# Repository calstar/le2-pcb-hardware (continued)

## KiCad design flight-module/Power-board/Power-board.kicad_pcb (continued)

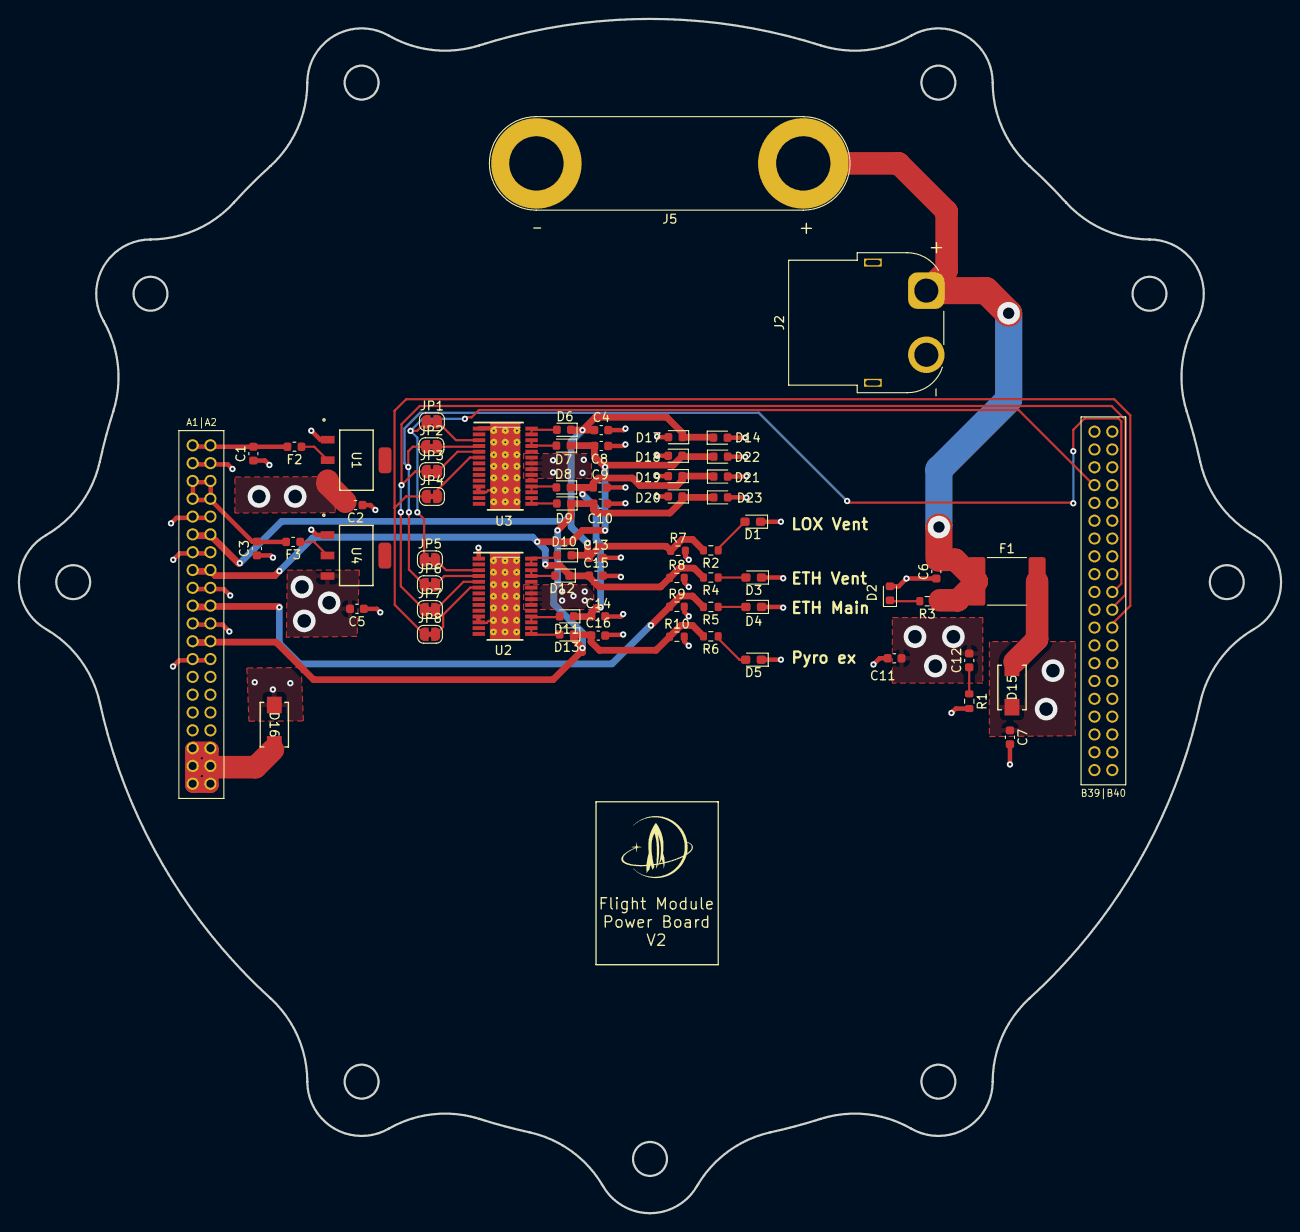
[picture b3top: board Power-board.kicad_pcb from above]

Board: 4 copper layers, 141.7 x 134.1 mm, 67 parts (0 on the bottom side), 40 nets.

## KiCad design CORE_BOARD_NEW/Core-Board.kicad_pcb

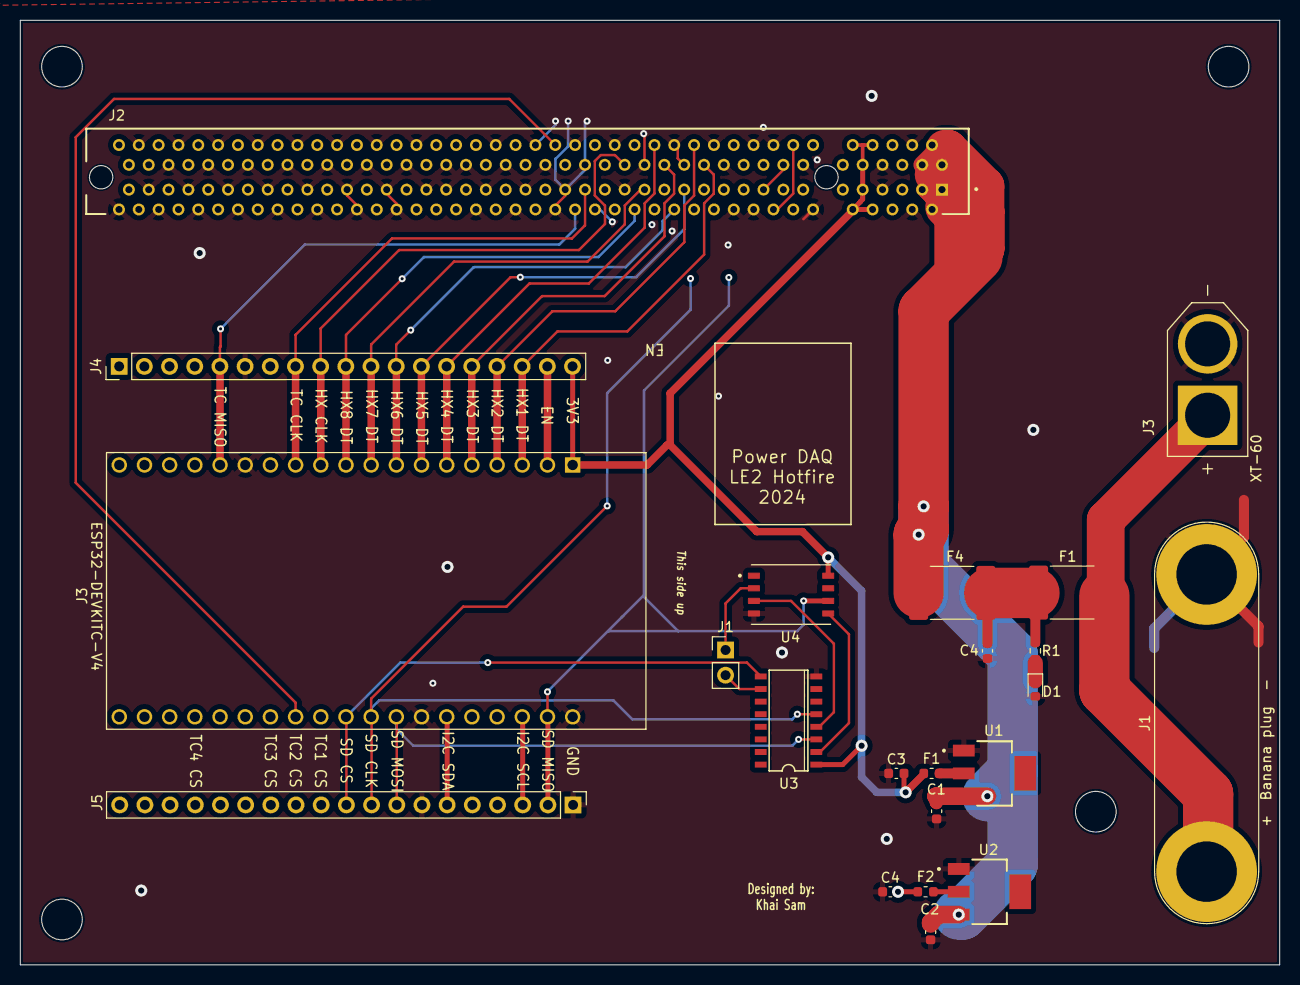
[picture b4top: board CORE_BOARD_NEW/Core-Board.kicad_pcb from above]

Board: 4 copper layers, 127.0 x 95.2 mm, 22 parts (0 on the bottom side), 35 nets.

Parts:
C1, C2: 10uF; C_0603_1608Metric
C3, C4, C4#2: 22uF; C_0603_1608Metric
D1: D_Small; D_0603_1608Metric
F1, F2: 500mA Fuse; Fuse_0603_1608Metric
F1#2, F4: 6A Fuse; Fuse_2920_7451Metric
J1: POWER; Banana_Jack_2Pin
J1#2: Pin Jumper; PinHeader_1x02_P2.54mm_Vertical
J2: Bus_PCI_Express_x16; SAMTEC_PCIE-164-02-F-D-TH-TR
J3: ESP32-DEVKITC-32D; MODULE_ESP32-DEVKITC-32D
J3#2: XT60-M; AMASS_XT60-M
J4, J5: Conn_01x19_Male; PinHeader_1x19_P2.54mm_Vertical
R1: 10k; R_0603_1608Metric
U1: AZ1117IH-3.3TRG1; SOT230P700X185-4N
U2: AZ1117IH-5TRG1; SOT230P700X185-4N
U3: 74HC4050D; SO16
U4: XTSD04GLGEAG; SON127P600X800X95-8N

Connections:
3.3V: C3.2, F1.2, J2.A8 (3.3V), J2.A9 (+3.3V), J2.A10 (3.3VAux), J2.B8 (+3.3V), J2.B9 (3.3V), J2.B10 (3.3Vaux), J3.1 (3V3), J4.19, U3.1 (VCC), U4.8 (VDD)
5V: C4.2, F2.2, J2.A5 (5V), J2.A6 (5V), J2.B5 (5V), J2.B6 (5V), J3.19 (EXT_5V), J4.1
12V: C1.2, C2.2, F4.2, J2.A1 (+12V), J2.A2 (+12V), J2.A3 (+12V), J2.B1 (+12V), J2.B2 (+12V), J2.B3 (+12V), U1.3 (INPUT), U2.3 (INPUT)
+12V: F1#2.1, J1.1, J3#2.P (POS)
EN: J3.2 (EN), J4.18
GND: C1.1, C2.1, C3.1, C4.1, C4#2.1, D1.2 (A), J1.2, J2.A4 (GND), J2.A7 (GND), J2.A12 (GND), J2.A15 (GND), J2.A18 (GND), J2.A20 (GND), J2.A23 (GND), J2.A24 (GND), J2.A27 (GND), J2.A28 (GND), J2.A31 (GND), J2.A34 (GND), J2.A37 (GND), J2.A38 (GND), J2.A41 (GND), J2.A42 (GND), J2.A45 (GND), J2.A46 (GND), J2.A49 (GND), J2.A51 (GND), J2.A54 (GND), J2.A55 (GND), J2.A58 (GND), J2.A59 (GND), J2.A62 (GND), J2.A63 (GND), J2.A66 (GND), J2.A67 (GND), J2.A70 (GND), J2.A71 (GND), J2.A74 (GND), J2.A75 (GND), J2.A78 (GND), J2.A79 (GND), J2.A82 (GND), J2.B4 (GND), J2.B7 (GND), J2.B13 (GND), J2.B16 (GND), J2.B18 (GND), J2.B21 (GND), J2.B22 (GND), J2.B25 (GND), J2.B26 (GND), J2.B29 (GND), J2.B32 (GND), J2.B35 (GND), J2.B36 (GND), J2.B39 (GND), J2.B40 (GND), J2.B43 (GND), J2.B44 (GND), J2.B47 (GND), J2.B49 (GND), J2.B52 (GND), J2.B53 (GND), J2.B56 (GND), J2.B57 (GND), J2.B60 (GND), J2.B61 (GND), J2.B64 (GND), J2.B65 (GND), J2.B68 (GND), J2.B69 (GND), J2.B72 (GND), J2.B73 (GND), J2.B76 (GND), J2.B77 (GND), J2.B80 (GND), J3.14 (GND1), J3.20 (GND3), J3.26 (GND2), J3#2.N (NEG), J4.6, J5.1, J5.7, U1.1 (GND), U2.1 (GND), U3.8 (GND), U4.4 (VSS)
HX1: J2.B23 (HX_DT1), J3.3 (SENSOR_VP), J4.17
HX2: J2.B24 (HX_DT2), J3.4 (SENSOR_VN), J4.16
HX3: J2.B27 (HX_DT3), J3.5 (IO34), J4.15
HX4: J2.B28 (HX_DT4), J3.6 (IO35), J4.14
HX5: J2.A25 (HX_DT5), J3.7 (IO32), J4.13
HX6: J2.A26 (HX_DT6), J3.8 (IO33), J4.12
HX7: J2.A29 (HX_DT7), J3.9 (IO25), J4.11
HX8: J2.A30 (HX_DT8), J3.10 (IO26), J4.10
HX CLK: J2.B31 (HX_CLK), J3.11 (IO27), J4.9
I2C SCL: J2.A16 (I2C_SCL_AUX), J2.B14 (I2C_SCL), J3.22 (IO22), J5.3
I2C SDA: J2.A17 (I2C_SDA_AUX), J2.B15 (I2C_SDA), J3.25 (IO21), J5.6
unnamed: C4#2.2, F1#2.2, F4.1, R1.1
unnamed: D1.1 (K), R1.2
unnamed: J1#2.1, U4.2 (SD3/~CS)
unnamed: F1.1, U1.2 (OUTPUT)
unnamed: F2.1, U2.2 (OUTPUT)
SD CLK_3.3: U3.4 (2Y), U4.3 (CLK)
SD CS_3.3: J1#2.2, U3.10 (4Y)
SD MOSI_3.3: U3.2 (1Y), U4.5 (CMD/DI)
SPI0 CLK: J2.B33 (SPI0_CLK), J3.28 (IO18), J5.9, U3.5 (2A)
SPI0 CS: J3.29 (IO5), J5.10, U3.9 (4A)
SPI0 MISO: J2.B34 (SPI0_MISO), J3.21 (IO23), J5.2, U4.6 (SD0/DO)
SPI0 MOSI: J3.27 (IO19), J5.8, U3.3 (1A)
SPI1 CLK: J2.A35 (SPI1_CLK), J3.12 (IO14), J4.8
SPI1 MISO: J2.A36 (SPI1_MISO), J3.15 (IO13), J4.5
TC CS 1: J2.B37 (TC_CS1), J3.30 (IO17)
TC CS 2: J2.B38 (TC_CS2), J3.31 (IO16)
TC CS 3: J2.A39 (TC_CS3), J3.32 (IO4)
TC CS 4: J2.A40 (TC_CS4), J3.35 (IO15)

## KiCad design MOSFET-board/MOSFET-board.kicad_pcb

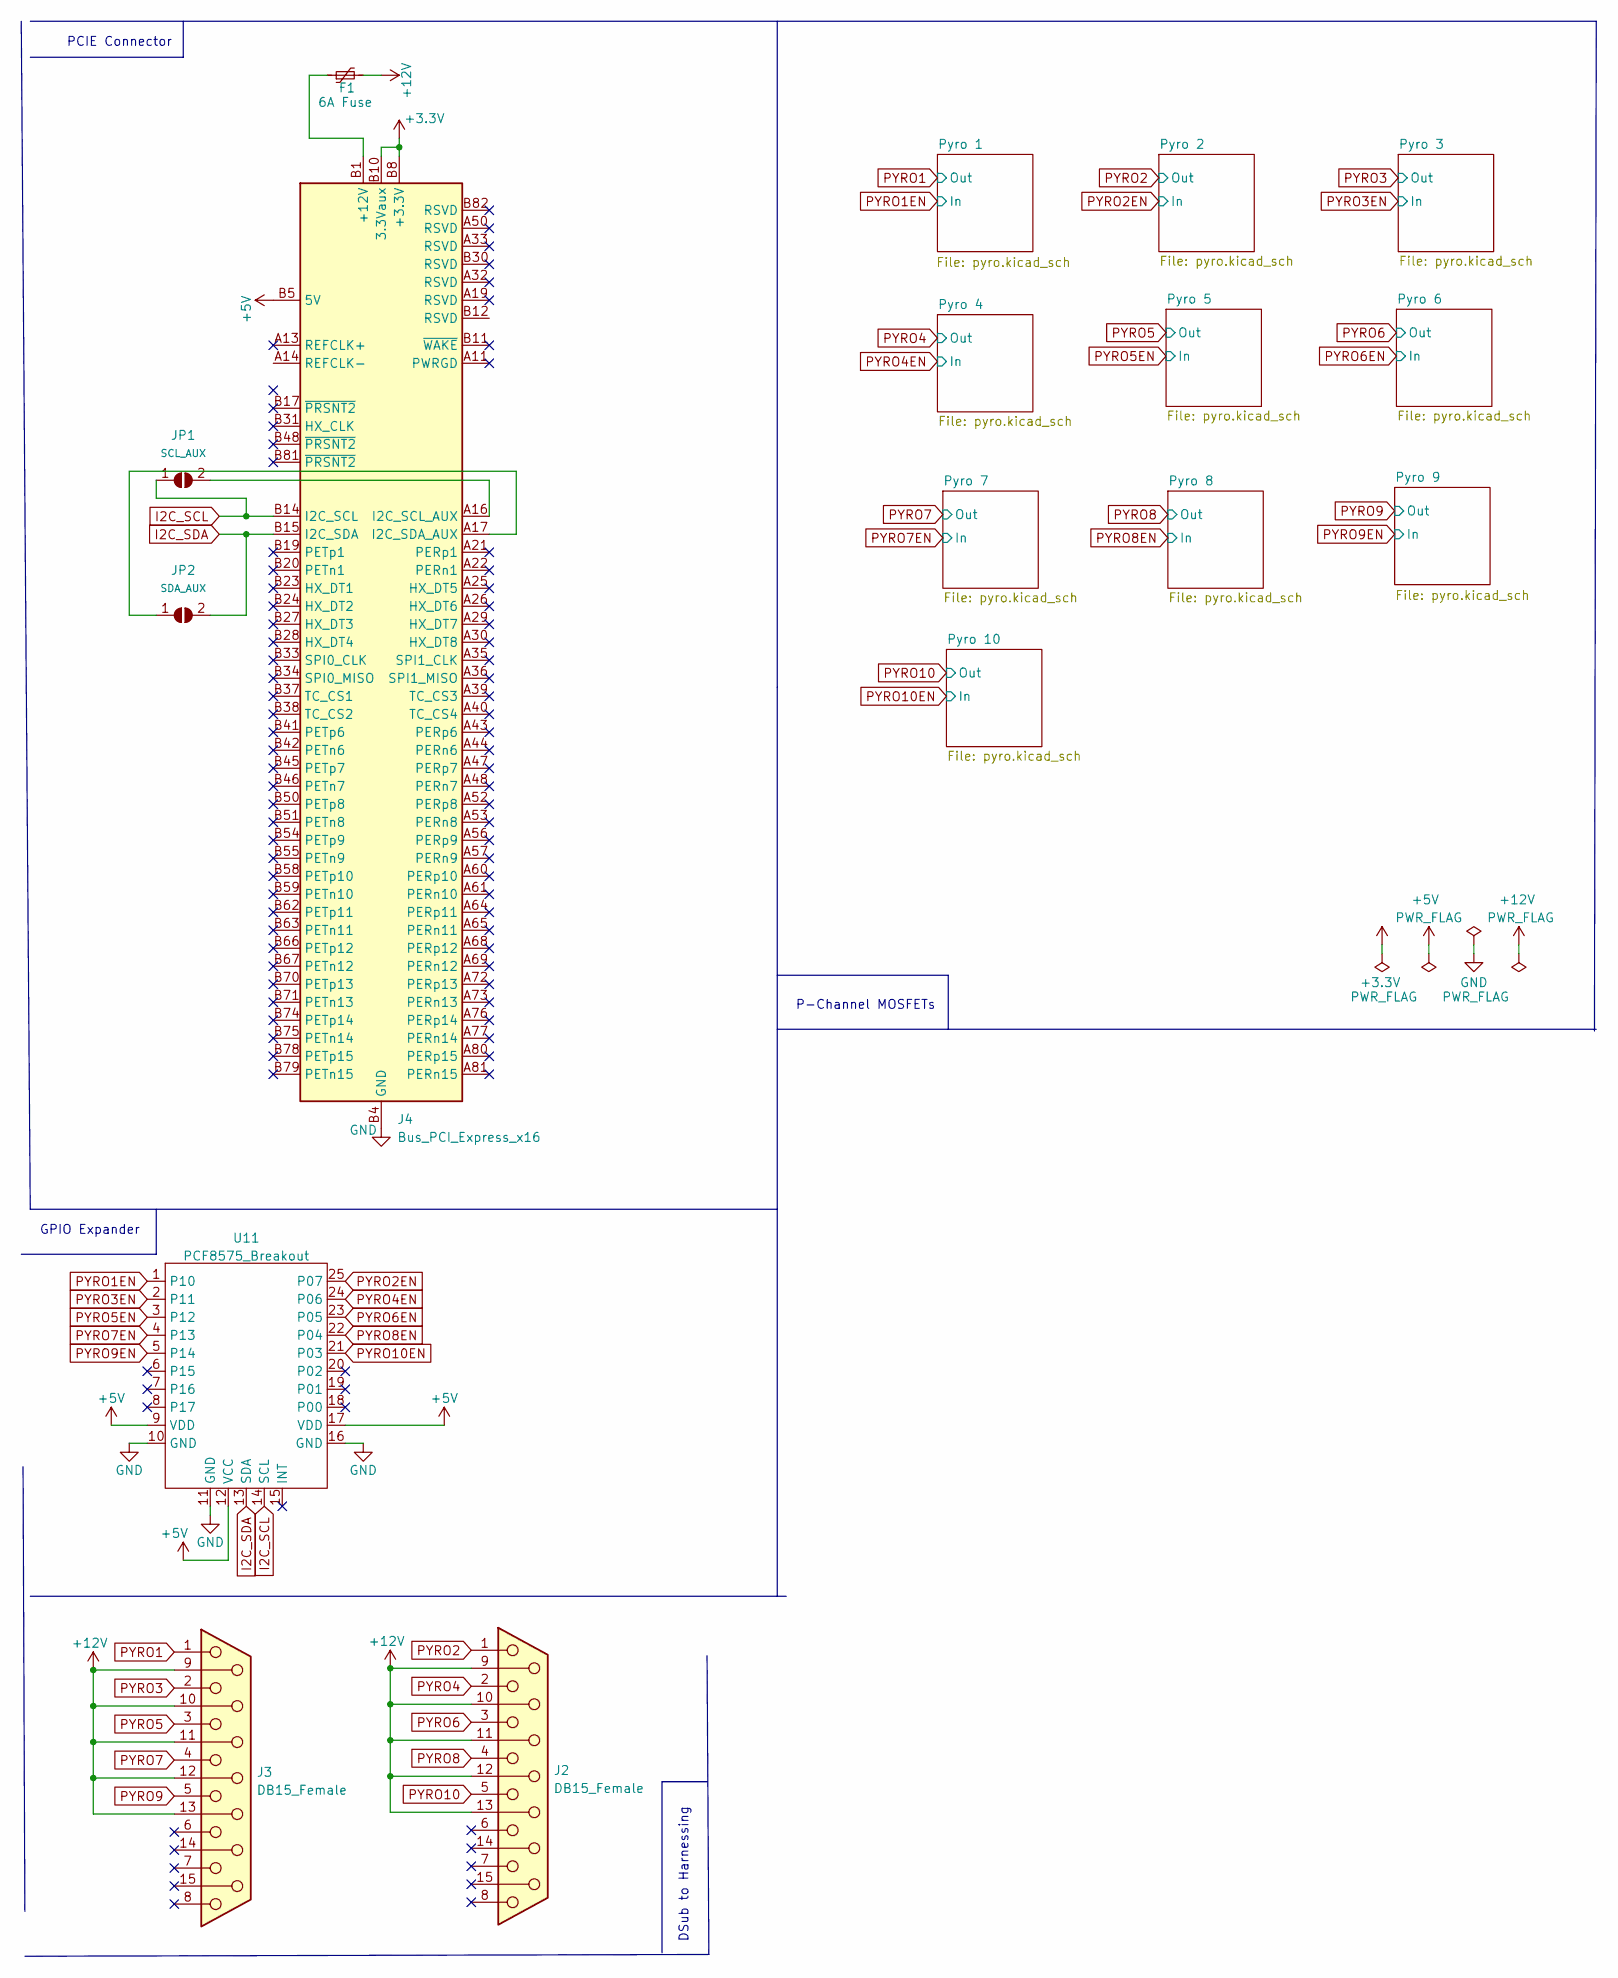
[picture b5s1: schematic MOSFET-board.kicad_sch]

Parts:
F1: 6A Fuse; Fuse_2920_7451Metric
J2, J3: DB15_Female; DSUB-15_Female_Horizontal_P2.77x2.84mm_EdgePinOffset7.70mm_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
J4: Bus_PCI_Express_x16; Custom-16x-PCIELock
JP1: SCL_AUX; SolderJumper-2_P1.3mm_Open_Pad1.0x1.5mm
JP2: SDA_AUX; SolderJumper-2_P1.3mm_Open_Pad1.0x1.5mm
U11: PCF8575_Breakout

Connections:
+3.3V: J4.A8 (3.3V), J4.A9 (+3.3V), J4.A10 (3.3VAux), J4.B8 (+3.3V), J4.B9 (3.3V), J4.B10 (3.3Vaux)
+5V: J4.A5 (5V), J4.A6 (5V), J4.B5 (5V), J4.B6 (5V), U11.9 (VDD), U11.12 (VCC), U11.17 (VDD); also elsewhere on the board
+12V: F1.2, J2.9, J2.10, J2.11 (P111), J2.12, J2.13, J3.9, J3.10, J3.11 (P111), J3.12, J3.13; also elsewhere on the board
GND: J4.A4 (GND), J4.A7 (GND), J4.A12 (GND), J4.A15 (GND), J4.A18 (GND), J4.A20 (GND), J4.A23 (GND), J4.A24 (GND), J4.A27 (GND), J4.A28 (GND), J4.A31 (GND), J4.A34 (GND), J4.A37 (GND), J4.A38 (GND), J4.A41 (GND), J4.A42 (GND), J4.A45 (GND), J4.A46 (GND), J4.A49 (GND), J4.A51 (GND), J4.A54 (GND), J4.A55 (GND), J4.A58 (GND), J4.A59 (GND), J4.A62 (GND), J4.A63 (GND), J4.A66 (GND), J4.A67 (GND), J4.A70 (GND), J4.A71 (GND), J4.A74 (GND), J4.A75 (GND), J4.A78 (GND), J4.A79 (GND), J4.A82 (GND), J4.B4 (GND), J4.B7 (GND), J4.B13 (GND), J4.B16 (GND), J4.B18 (GND), J4.B21 (GND), J4.B22 (GND), J4.B25 (GND), J4.B26 (GND), J4.B29 (GND), J4.B32 (GND), J4.B35 (GND), J4.B36 (GND), J4.B39 (GND), J4.B40 (GND), J4.B43 (GND), J4.B44 (GND), J4.B47 (GND), J4.B49 (GND), J4.B52 (GND), J4.B53 (GND), J4.B56 (GND), J4.B57 (GND), J4.B60 (GND), J4.B61 (GND), J4.B64 (GND), J4.B65 (GND), J4.B68 (GND), J4.B69 (GND), J4.B72 (GND), J4.B73 (GND), J4.B76 (GND), J4.B77 (GND), J4.B80 (GND), U11.10 (GND), U11.11 (GND), U11.16 (GND); also elsewhere on the board
I2C_SCL: J4.B14 (I2C_SCL), JP1.1 (A), U11.14 (SCL)
I2C_SDA: J4.B15 (I2C_SDA), JP2.2 (B), U11.13 (SDA)
unnamed: F1.1, J4.A1 (+12V), J4.A2 (+12V), J4.A3 (+12V), J4.B1 (+12V), J4.B2 (+12V), J4.B3 (+12V)
unnamed: J4.A16 (I2C_SCL_AUX), JP1.2 (B)
unnamed: J4.A17 (I2C_SDA_AUX), JP2.1 (A)
PYRO1: J3.1; also elsewhere on the board
PYRO1EN: U11.1 (P10); also elsewhere on the board
PYRO2: J2.1; also elsewhere on the board
PYRO2EN: U11.25 (P07); also elsewhere on the board
PYRO3: J3.2; also elsewhere on the board
PYRO3EN: U11.2 (P11); also elsewhere on the board
PYRO4: J2.2; also elsewhere on the board
PYRO4EN: U11.24 (P06); also elsewhere on the board
PYRO5: J3.3; also elsewhere on the board
PYRO5EN: U11.3 (P12); also elsewhere on the board
PYRO6: J2.3; also elsewhere on the board
PYRO6EN: U11.23 (P05); also elsewhere on the board
PYRO7: J3.4; also elsewhere on the board
PYRO7EN: U11.4 (P13); also elsewhere on the board
PYRO8: J2.4; also elsewhere on the board
PYRO8EN: U11.22 (P04); also elsewhere on the board
PYRO9: J3.5; also elsewhere on the board
PYRO9EN: U11.5 (P14); also elsewhere on the board
PYRO10: J2.5; also elsewhere on the board
PYRO10EN: U11.21 (P03); also elsewhere on the board

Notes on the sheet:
GPIO Expander
P-Channel MOSFETs
DSub to Harnessing
PCIE Connector

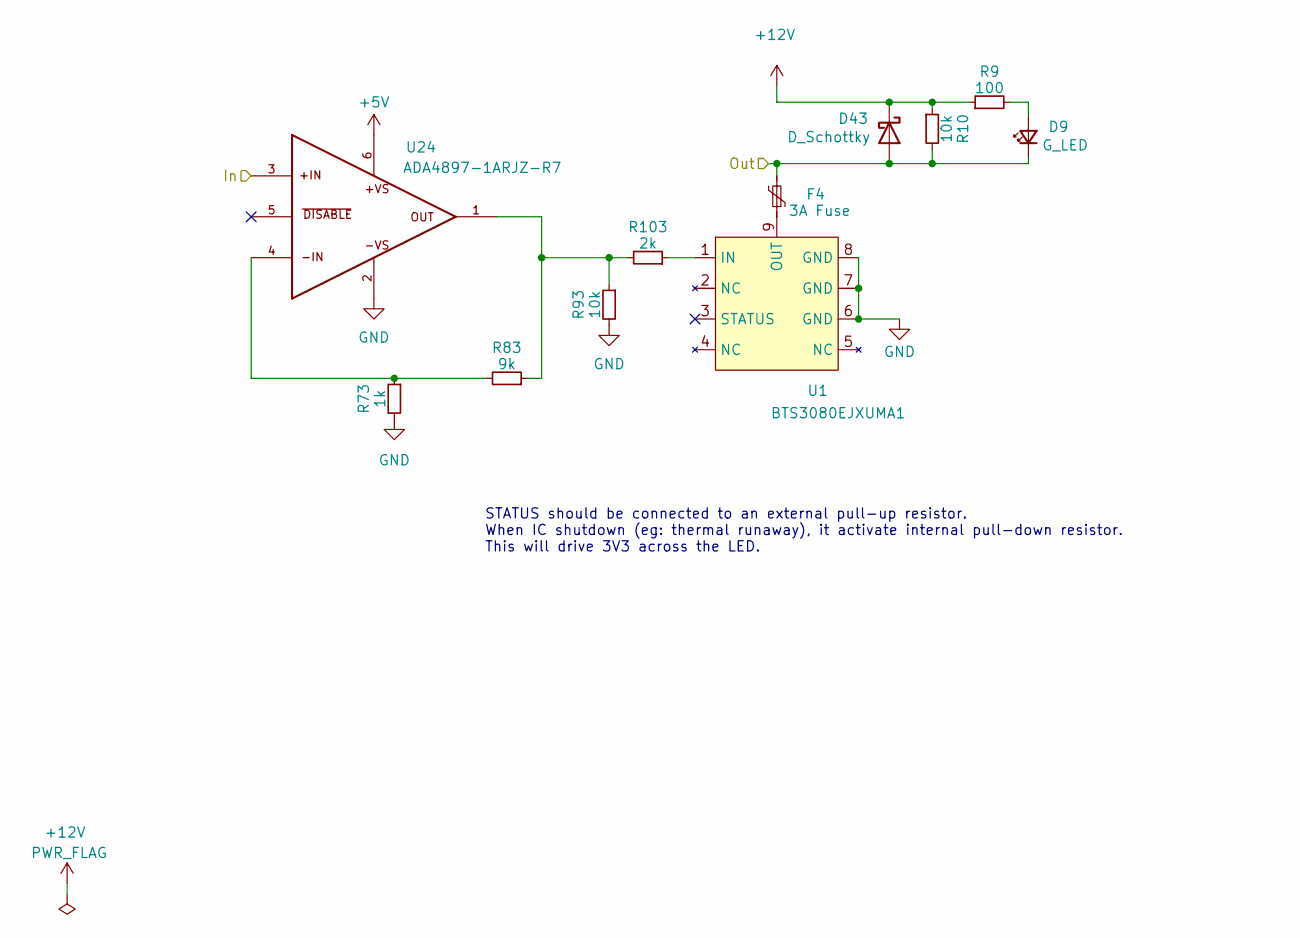
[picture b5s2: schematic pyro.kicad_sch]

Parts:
D9: G_LED; LED_0603_1608Metric
D43: D_Schottky; D_0603_1608Metric
F4: 3A Fuse; Fuse_2920_7451Metric
R9: 100; R_0603_1608Metric
R10, R93: 10k; R_0603_1608Metric
R73: 1k; R_0603_1608Metric
R83: 9k; R_0603_1608Metric
R103: 2k; R_0603_1608Metric
U1: BTS3080EJXUMA1; SOIC127P600X115-9N
U24: ADA4897-1ARJZ-R7; SOT95P280X145-6N; PARTREV B

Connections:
+5V: U24.6; also elsewhere on the board
+12V: D43.1 (K), R9.1, R10.1; also elsewhere on the board
GND: R73.2, R93.2, U1.6 (GND), U1.7 (GND), U1.8 (GND), U24.2; also elsewhere on the board
unnamed: D9.2 (A), R9.2
unnamed: R73.1, R83.2, U24.4
unnamed: R83.1, R93.1, R103.2, U24.1
unnamed: R103.1, U1.1 (IN)
unnamed: F4.1, U1.9 (OUT)
PYRO1: D9.1 (K), D43.2 (A), F4.2, R10.2; also elsewhere on the board
PYRO1EN: U24.3; also elsewhere on the board

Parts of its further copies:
D1, D5, D13, D17, D21, D25, D29, D33, D37: G_LED; LED_0603_1608Metric
D41, D42, D44, D45, D46, D47, D48, D49, D50: D_Schottky; D_0603_1608Metric
F2, F3, F5, F6, F7, F8, F9, F10, F11: 3A Fuse; Fuse_2920_7451Metric
R1, R5, R13, R17, R21, R25, R29, R33, R37: 100; R_0603_1608Metric
R2, R6, R14, R18, R22, R26, R30, R34, R38, R91, R92, R94, R95, R96, R97, R98, R99, R100: 10k; R_0603_1608Metric
R71, R72, R74, R75, R76, R77, R78, R79, R80: 1k; R_0603_1608Metric
R81, R82, R84, R85, R86, R87, R88, R89, R90: 9k; R_0603_1608Metric
R101, R102, R104, R105, R106, R107, R108, R109, R110: 2k; R_0603_1608Metric
U2, U3, U4, U5, U6, U7, U8, U9, U10: BTS3080EJXUMA1; SOIC127P600X115-9N
U22, U23, U25, U26, U27, U28, U29, U30, U31: ADA4897-1ARJZ-R7; SOT95P280X145-6N; PARTREV B

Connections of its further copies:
+5V: U22.6, U23.6, U25.6, U26.6, U27.6, U28.6, U29.6, U30.6, U31.6; also elsewhere on the board
+12V: D41.1 (K), D42.1 (K), D44.1 (K), D45.1 (K), D46.1 (K), D47.1 (K), D48.1 (K), D49.1 (K), D50.1 (K), R1.1, R2.1, R5.1, R6.1, R13.1, R14.1, R17.1, R18.1, R21.1, R22.1, R25.1, R26.1, R29.1, R30.1, R33.1, R34.1, R37.1, R38.1; also elsewhere on the board
GND: R71.2, R72.2, R74.2, R75.2, R76.2, R77.2, R78.2, R79.2, R80.2, R91.2, R92.2, R94.2, R95.2, R96.2, R97.2, R98.2, R99.2, R100.2, U2.6 (GND), U2.7 (GND), U2.8 (GND), U3.6 (GND), U3.7 (GND), U3.8 (GND), U4.6 (GND), U4.7 (GND), U4.8 (GND), U5.6 (GND), U5.7 (GND), U5.8 (GND), U6.6 (GND), U6.7 (GND), U6.8 (GND), U7.6 (GND), U7.7 (GND), U7.8 (GND), U8.6 (GND), U8.7 (GND), U8.8 (GND), U9.6 (GND), U9.7 (GND), U9.8 (GND), U10.6 (GND), U10.7 (GND), U10.8 (GND), U22.2, U23.2, U25.2, U26.2, U27.2, U28.2, U29.2, U30.2, U31.2; also elsewhere on the board
unnamed: D1.2 (A), R1.2
unnamed: D5.2 (A), R5.2
unnamed: D13.2 (A), R13.2
unnamed: D17.2 (A), R17.2
unnamed: D21.2 (A), R21.2
unnamed: D25.2 (A), R25.2
unnamed: D29.2 (A), R29.2
unnamed: D33.2 (A), R33.2
unnamed: D37.2 (A), R37.2
unnamed: R71.1, R81.2, U22.4
unnamed: R72.1, R82.2, U23.4
unnamed: R74.1, R84.2, U25.4
unnamed: R75.1, R85.2, U26.4
unnamed: R76.1, R86.2, U27.4
unnamed: R77.1, R87.2, U28.4
unnamed: R78.1, R88.2, U29.4
unnamed: R79.1, R89.2, U30.4
unnamed: R80.1, R90.2, U31.4
unnamed: R90.1, R100.1, R110.2, U31.1
unnamed: R81.1, R91.1, R101.2, U22.1
unnamed: R82.1, R92.1, R102.2, U23.1
unnamed: R84.1, R94.1, R104.2, U25.1
unnamed: R85.1, R95.1, R105.2, U26.1
unnamed: R86.1, R96.1, R106.2, U27.1
unnamed: R87.1, R97.1, R107.2, U28.1
unnamed: R88.1, R98.1, R108.2, U29.1
unnamed: R89.1, R99.1, R109.2, U30.1
unnamed: R109.1, U2.1 (IN)
unnamed: F10.1, U2.9 (OUT)
unnamed: R104.1, U3.1 (IN)
unnamed: F5.1, U3.9 (OUT)
unnamed: R110.1, U4.1 (IN)
unnamed: F11.1, U4.9 (OUT)
unnamed: R105.1, U5.1 (IN)
unnamed: F6.1, U5.9 (OUT)
unnamed: R106.1, U6.1 (IN)
unnamed: F7.1, U6.9 (OUT)
unnamed: R101.1, U7.1 (IN)
unnamed: F2.1, U7.9 (OUT)
unnamed: R107.1, U8.1 (IN)
unnamed: F8.1, U8.9 (OUT)
unnamed: R102.1, U9.1 (IN)
unnamed: F3.1, U9.9 (OUT)
unnamed: R108.1, U10.1 (IN)
unnamed: F9.1, U10.9 (OUT)
PYRO2: D33.1 (K), D49.2 (A), F10.2, R34.2; also elsewhere on the board
PYRO2EN: U30.3; also elsewhere on the board
PYRO3: D13.1 (K), D44.2 (A), F5.2, R14.2; also elsewhere on the board
PYRO3EN: U25.3; also elsewhere on the board
PYRO4: D37.1 (K), D50.2 (A), F11.2, R38.2; also elsewhere on the board
PYRO4EN: U31.3; also elsewhere on the board
PYRO5: D17.1 (K), D45.2 (A), F6.2, R18.2; also elsewhere on the board
PYRO5EN: U26.3; also elsewhere on the board
PYRO6: D21.1 (K), D46.2 (A), F7.2, R22.2; also elsewhere on the board
PYRO6EN: U27.3; also elsewhere on the board
PYRO7: D1.1 (K), D41.2 (A), F2.2, R2.2; also elsewhere on the board
PYRO7EN: U22.3; also elsewhere on the board
PYRO8: D25.1 (K), D47.2 (A), F8.2, R26.2; also elsewhere on the board
PYRO8EN: U28.3; also elsewhere on the board
PYRO9: D5.1 (K), D42.2 (A), F3.2, R6.2; also elsewhere on the board
PYRO9EN: U23.3; also elsewhere on the board
PYRO10: D29.1 (K), D48.2 (A), F9.2, R30.2; also elsewhere on the board
PYRO10EN: U29.3; also elsewhere on the board

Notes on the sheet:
STATUS should be connected to an external pull-up resistor. When IC shutdown (eg: thermal runaway), it activate internal pull-down resistor. This will drive 3V3 across the LED.

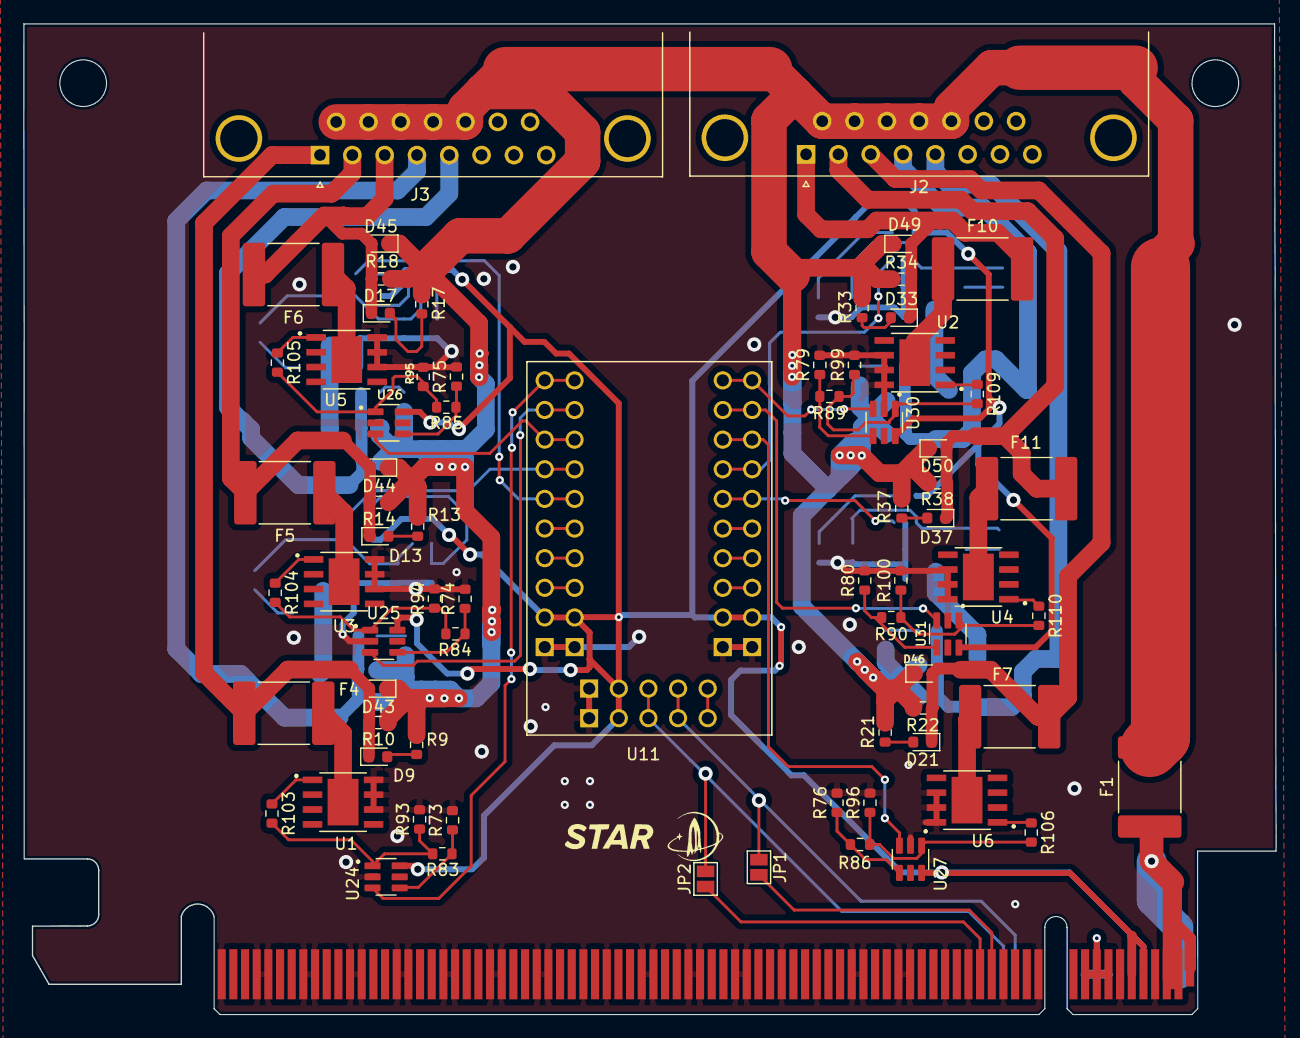
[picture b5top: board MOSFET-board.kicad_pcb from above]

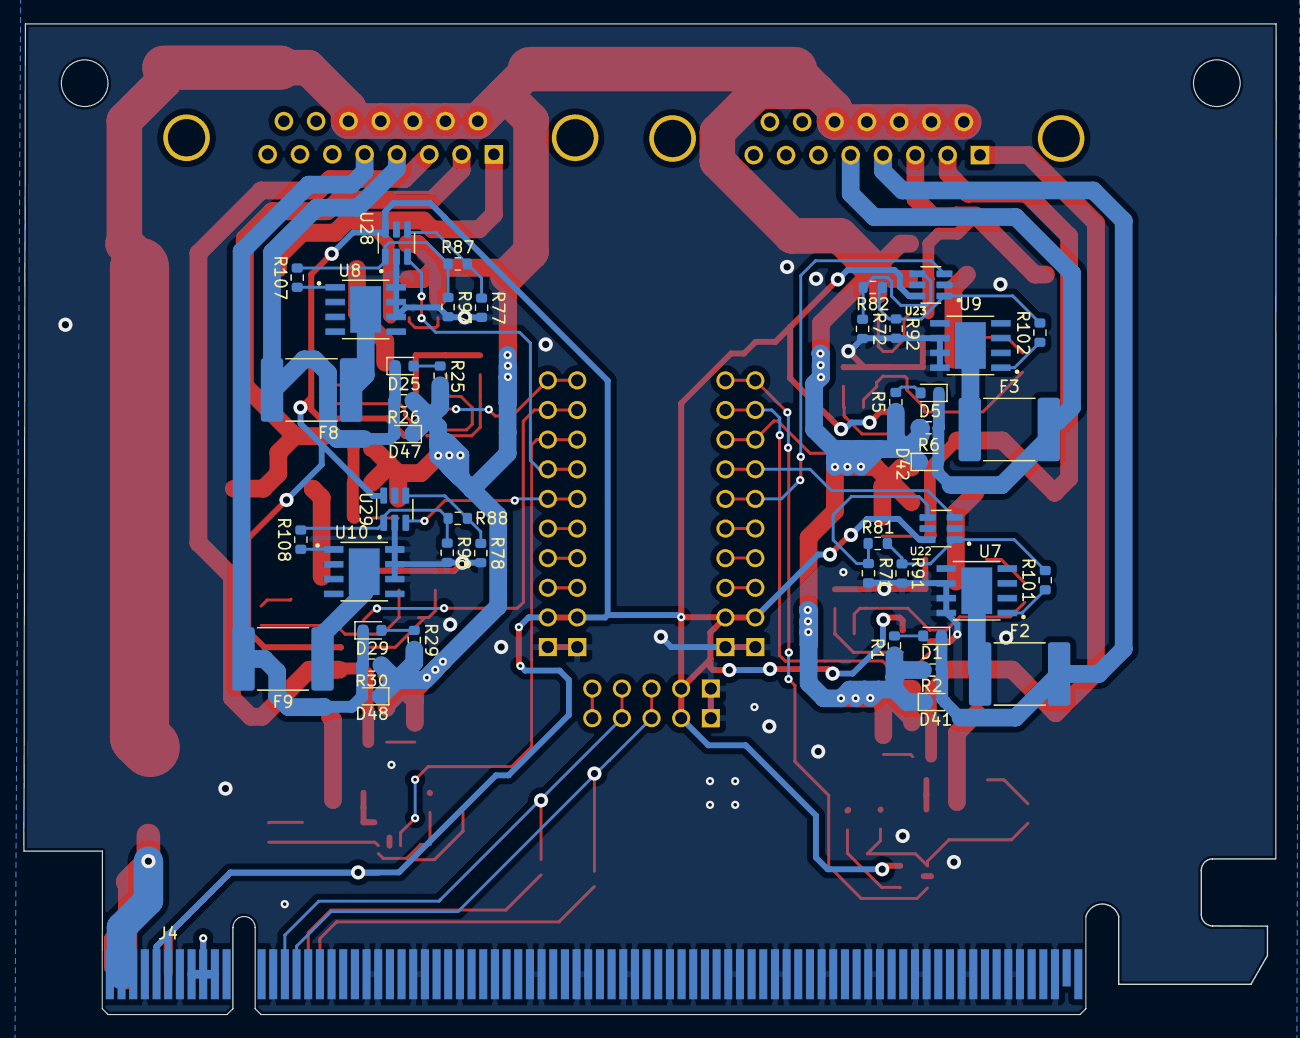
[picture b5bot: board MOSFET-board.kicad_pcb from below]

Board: 2 copper layers, 107.3 x 84.9 mm, 117 parts (45 on the bottom side), 79 nets.

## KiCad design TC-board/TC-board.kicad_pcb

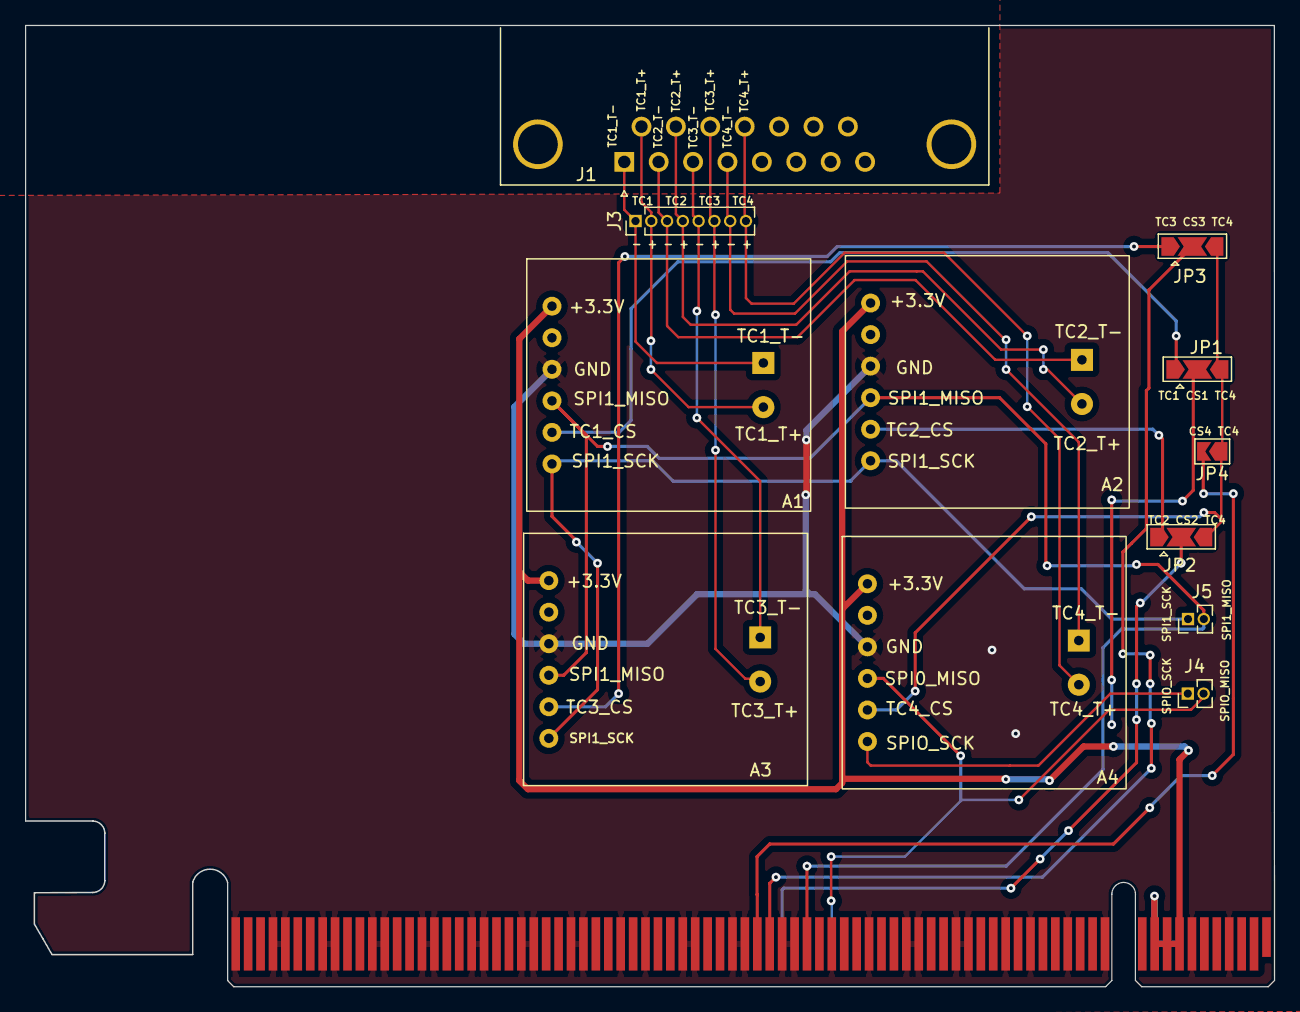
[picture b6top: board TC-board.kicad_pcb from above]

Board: 2 copper layers, 100.6 x 77.4 mm, 13 parts (1 on the bottom side), 22 nets.

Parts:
A1, A2, A3, A4: MAX31855_Breakout
J1: DB15_Female; DSUB_622-015-260-042
J2: PCIe_x16; Custom-16x-PCIELock
J3: Conn_01x08_Male; PinHeader_1x08_P1.27mm_Vertical
J4, J5: Conn_01x02_Male; PinHeader_1x02_P1.27mm_Vertical
JP1, JP2, JP3: SolderJumper_3_Open; SolderJumper-3_P2.0mm_Open_TrianglePad1.0x1.5mm
JP4: SolderJumper_2_Open; SolderJumper-2_P1.3mm_Open_TrianglePad1.0x1.5mm

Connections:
+3.3V: A1.4 (VIN), A2.4 (VIN), A3.4 (VIN), A4.4 (VIN), J2.A8 (3.3V), J2.A9 (+3.3V), J2.A10 (3.3VAux), J2.B8 (+3.3V), J2.B9 (3.3V), J2.B10 (3.3Vaux)
/SPI0_SCK: A4.5 (SCK), J4.1
/SPI1_SCK: A1.5 (SCK), A2.5 (SCK), A3.5 (SCK), J5.1
/TC1_CS: A1.6 (CS), JP1.1 (A)
/TC1_T+: A1.3 (T+), J1.9, J3.2
/TC1_T-: A1.2 (T-), J1.1, J3.1
/TC2_CS: A2.6 (CS), JP2.1 (A)
/TC2_T+: A2.3 (T+), J1.10, J3.4
/TC2_T-: A2.2 (T-), J1.2, J3.3
/TC3_CS: A3.6 (CS), JP3.1 (A)
/TC3_T+: A3.3 (T+), J1.11 (P111), J3.6
/TC3_T-: A3.2 (T-), J1.3, J3.5
/TC4_CS: A4.6 (CS), JP1.3 (B), JP2.3 (B), JP3.3 (B), JP4.1 (A)
/TC4_T+: A4.3 (T+), J1.12, J3.8
/TC4_T-: A4.2 (T-), J1.4, J3.7
CS1: J2.B37 (TC_CS1), JP1.2 (C)
CS2: J2.B38 (TC_CS2), JP2.2 (C)
CS3: J2.A39 (TC_CS3), JP3.2 (C)
CS4: J2.A40 (TC_CS4), JP4.2 (B)
GND: A1.1 (GND), A2.1 (GND), A3.1 (GND), A4.1 (GND), J2.A4 (GND), J2.A7 (GND), J2.A12 (GND), J2.A15 (GND), J2.A18 (GND), J2.A20 (GND), J2.A23 (GND), J2.A24 (GND), J2.A27 (GND), J2.A28 (GND), J2.A31 (GND), J2.A34 (GND), J2.A37 (GND), J2.A38 (GND), J2.A41 (GND), J2.A42 (GND), J2.A45 (GND), J2.A46 (GND), J2.A49 (GND), J2.A51 (GND), J2.A54 (GND), J2.A55 (GND), J2.A58 (GND), J2.A59 (GND), J2.A62 (GND), J2.A63 (GND), J2.A66 (GND), J2.A67 (GND), J2.A70 (GND), J2.A71 (GND), J2.A74 (GND), J2.A75 (GND), J2.A78 (GND), J2.A79 (GND), J2.A82 (GND), J2.B4 (GND), J2.B7 (GND), J2.B13 (GND), J2.B16 (GND), J2.B18 (GND), J2.B21 (GND), J2.B22 (GND), J2.B25 (GND), J2.B26 (GND), J2.B29 (GND), J2.B32 (GND), J2.B35 (GND), J2.B36 (GND), J2.B39 (GND), J2.B40 (GND), J2.B43 (GND), J2.B44 (GND), J2.B47 (GND), J2.B49 (GND), J2.B52 (GND), J2.B53 (GND), J2.B56 (GND), J2.B57 (GND), J2.B60 (GND), J2.B61 (GND), J2.B64 (GND), J2.B65 (GND), J2.B68 (GND), J2.B69 (GND), J2.B72 (GND), J2.B73 (GND), J2.B76 (GND), J2.B77 (GND), J2.B80 (GND)
SPI0_MISO: A4.7 (SDO), J2.B34 (SPI0_MISO), J4.2
SPI1_MISO: A1.7 (SDO), A2.7 (SDO), A3.7 (SDO), J2.A36 (SPI1_MISO), J5.2

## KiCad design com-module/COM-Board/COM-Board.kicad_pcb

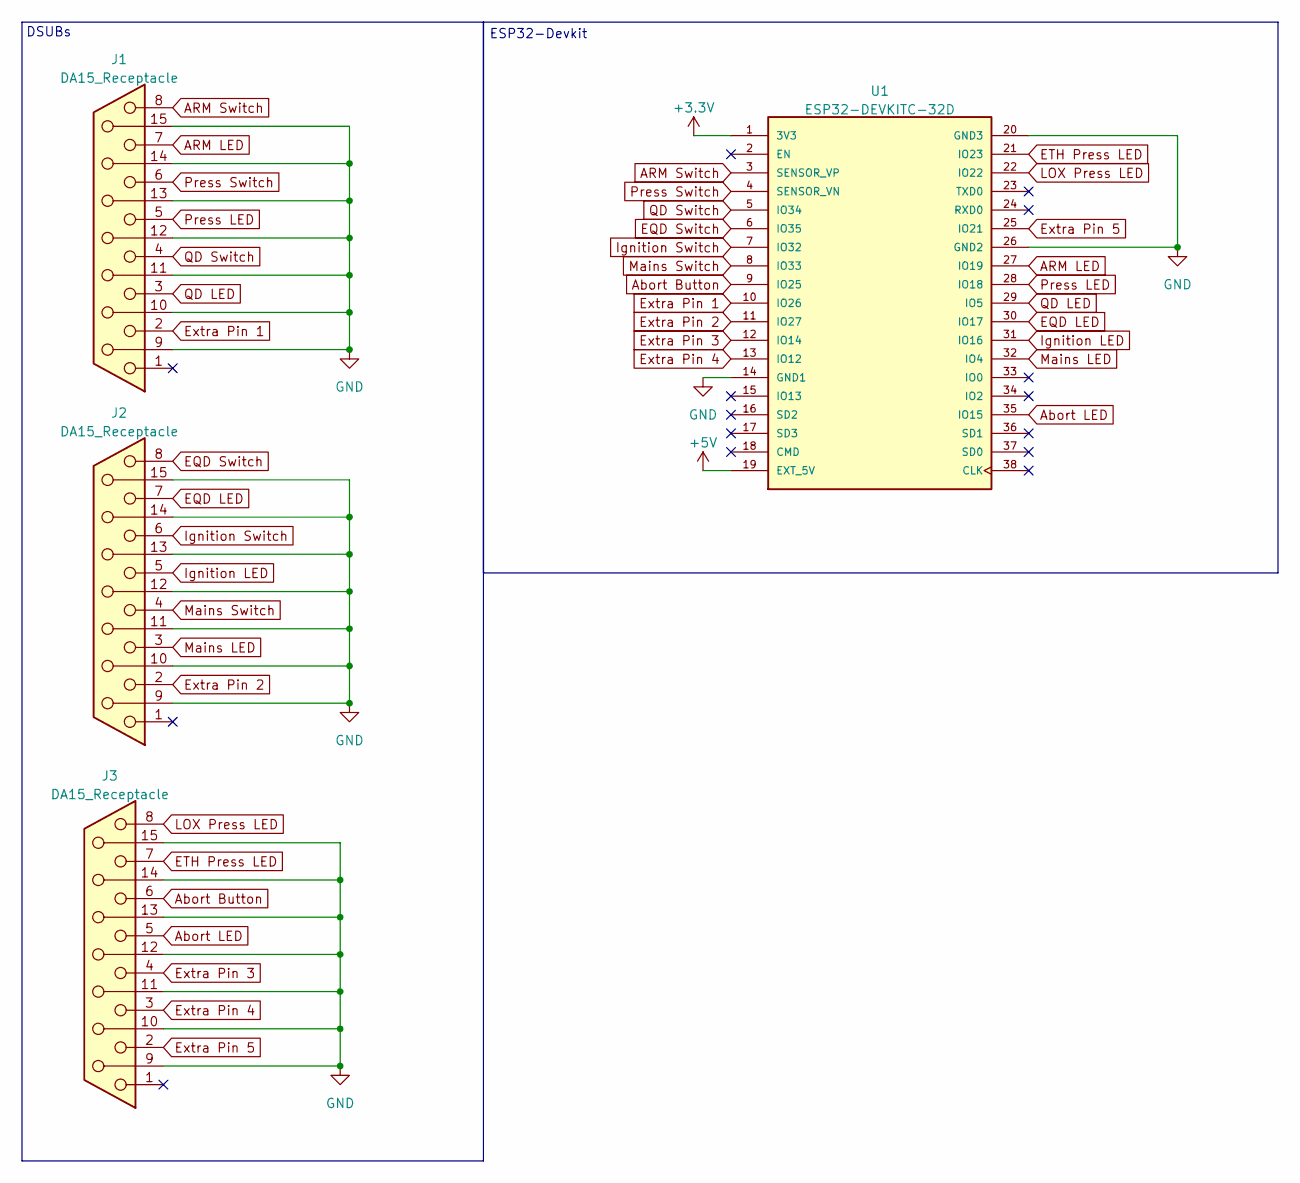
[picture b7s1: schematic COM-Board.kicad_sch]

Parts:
J1, J2, J3: DA15_Receptacle; DSUB-15_Female_Vertical_P2.77x2.84mm_MountingHoles
U1: ESP32-DEVKITC-32D; MODULE_ESP32-DEVKITC-32D; PARTREV 4

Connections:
+3.3V: U1.1 (3V3)
+5V: U1.19 (EXT_5V)
ARM LED: J1.7, U1.27 (IO19)
ARM Switch: J1.8, U1.3 (SENSOR_VP)
Abort Button: J3.6, U1.9 (IO25)
Abort LED: J3.5, U1.35 (IO15)
EQD LED: J2.7, U1.30 (IO17)
EQD Switch: J2.8, U1.6 (IO35)
ETH Press LED: J3.7, U1.21 (IO23)
Extra Pin 1: J1.2, U1.10 (IO26)
Extra Pin 2: J2.2, U1.11 (IO27)
Extra Pin 3: J3.4, U1.12 (IO14)
Extra Pin 4: J3.3, U1.13 (IO12)
Extra Pin 5: J3.2, U1.25 (IO21)
GND: J1.9, J1.10, J1.11 (P111), J1.12, J1.13, J1.14, J1.15, J2.9, J2.10, J2.11 (P111), J2.12, J2.13, J2.14, J2.15, J3.9, J3.10, J3.11 (P111), J3.12, J3.13, J3.14, J3.15, U1.14 (GND1), U1.20 (GND3), U1.26 (GND2)
Ignition LED: J2.5, U1.31 (IO16)
Ignition Switch: J2.6, U1.7 (IO32)
LOX Press LED: J3.8, U1.22 (IO22)
Mains LED: J2.3, U1.32 (IO4)
Mains Switch: J2.4, U1.8 (IO33)
Press LED: J1.5, U1.28 (IO18)
Press Switch: J1.6, U1.4 (SENSOR_VN)
QD LED: J1.3, U1.29 (IO5)
QD Switch: J1.4, U1.5 (IO34)

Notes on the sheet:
DSUBs
ESP32-Devkit
